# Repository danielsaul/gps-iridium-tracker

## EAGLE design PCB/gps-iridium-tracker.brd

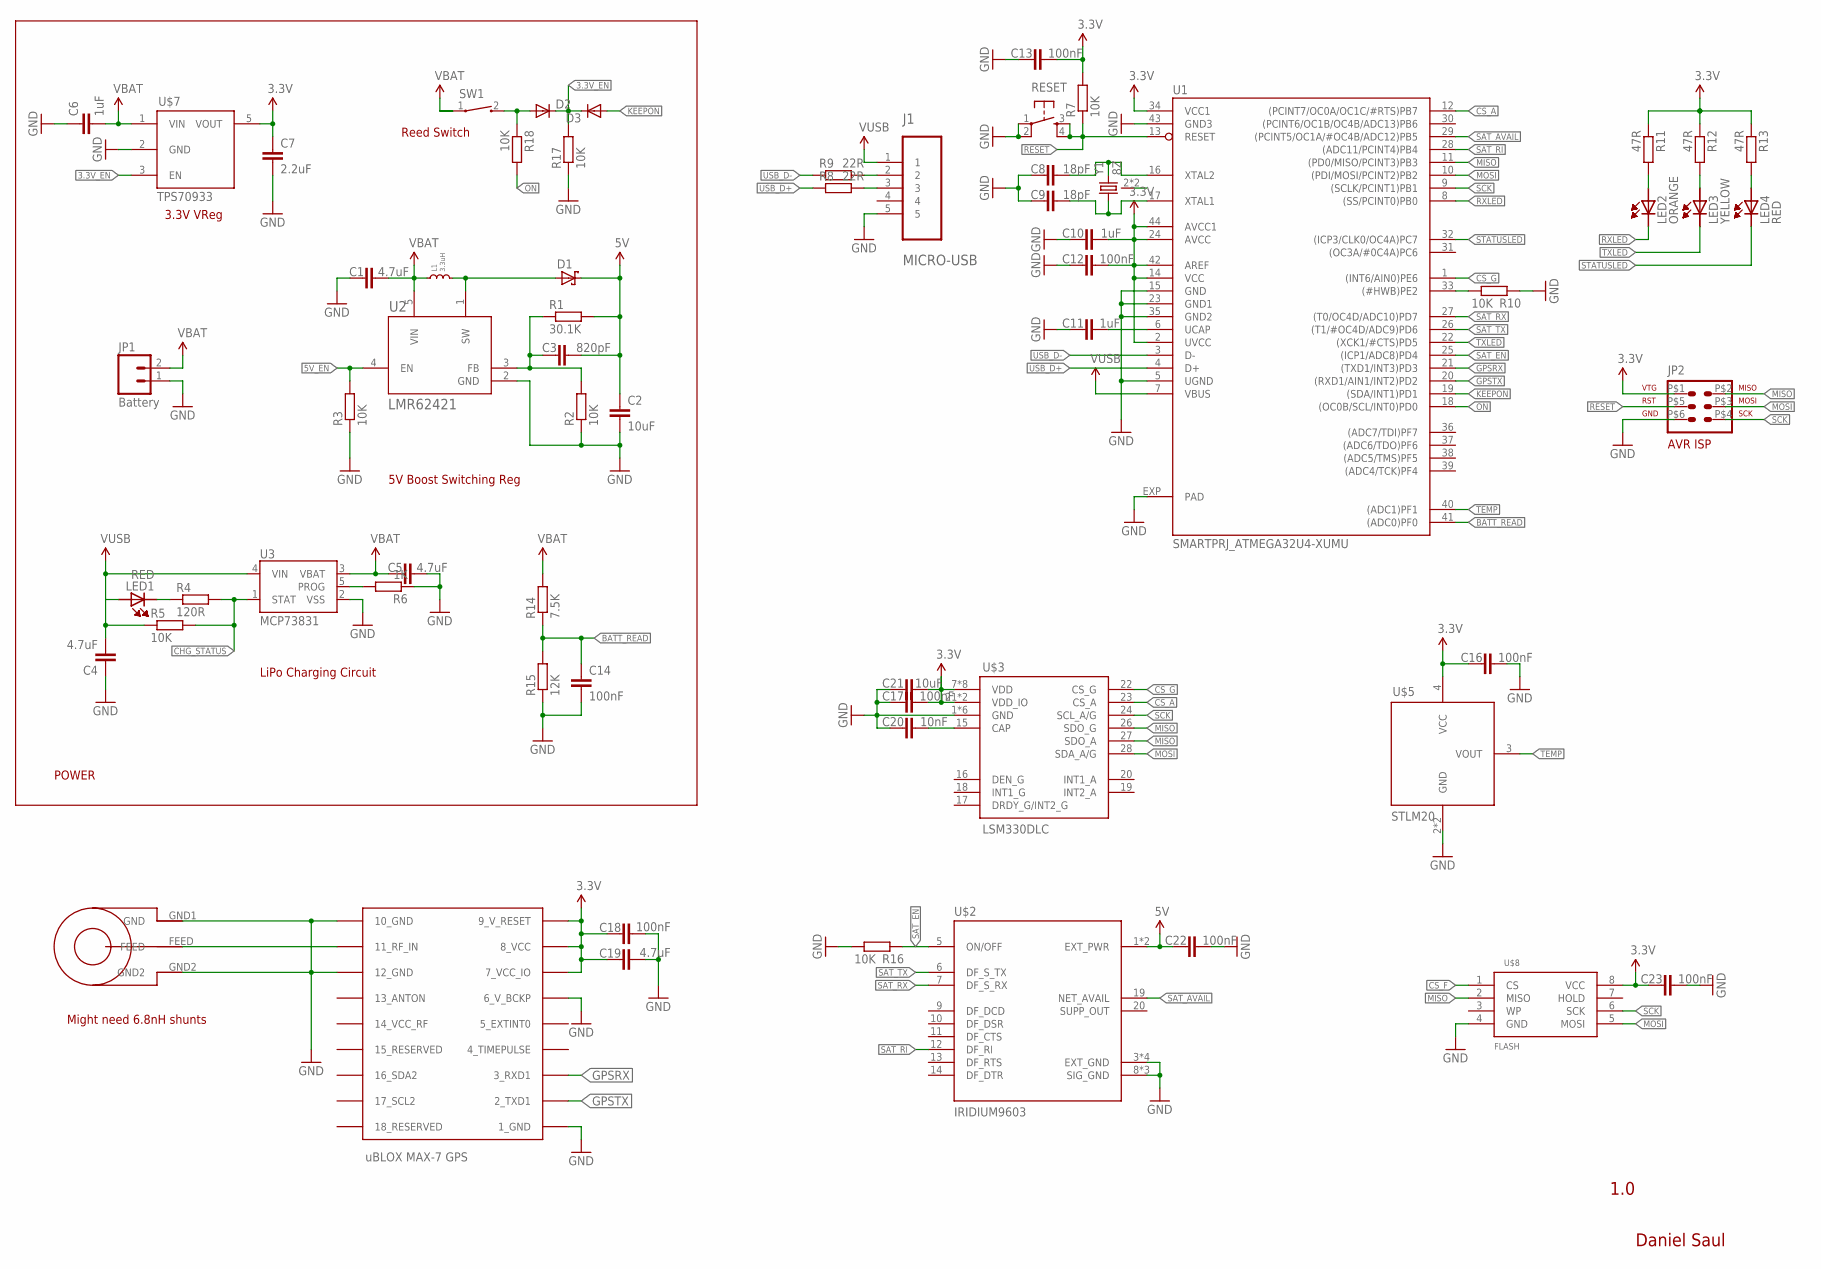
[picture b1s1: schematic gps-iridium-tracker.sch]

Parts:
C1, C4, C5: 4.7uF; 0603-CAP
C2: 10uF; 0603-CAP
C3: 820pF; 0603-CAP
C6: 1uF; 0603-CAP
C7: 2.2uF; 0603-CAP
C8, C9: 18pF; 0603-CAP
C10, C11: 1uF; 0402-CAP
C12, C13, C14, C16, C17, C18, C22, C23: 100nF; 0402-CAP
C19: 4.7uF; 0805
C20: 10nF; 0402-CAP
C21: 10uF; 0402-CAP
D1: B220A-13-F; SMA-DIODE
D2, D3: DIODESOD; SOD-323
GPS: UBLOX_MAX-6
J1: MICRO-USB; MOLEX_47346-0001
JP1: Battery; JST-2-PTH
JP2: AVR-ISP-6SMD; ICSPSMD
L1: 3.3uH; SRN3015
LED1, LED4: RED; R0402
LED2: ORANGE; R0402
LED3: YELLOW; R0402
R1: 30.1K; R0402
R2, R3, R5, R7, R10, R16, R17, R18: 10K; R0402
R4: 120R; R0402
R6: 1K; R0402
R8, R9: 22R; R0402
R11, R12, R13: 47R; R0402
R14: 7.5K; R0402
R15: 12K; R0402
RESET: KMR441NGLFS
SW1: CT10-XXXX-G1
U1: SMARTPRJ_ATMEGA32U4-XUMU; SMARTPRJ_QFN44ML7X7
U2: LMR62421; MF05A
U3: MCP73831; SOT23-5
U$1: JTI_ANTENNA-1575AT54A0010
U$2: IRIDIUM9603
U$3: LSM330DLC; LGA-28L
U$5: STLM20; SOT23-5L
U$7: TPS70933; SOT23-5L
U$8: FLASH; SO08
Y1: 8Z

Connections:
3.3V: C7.1, C10.2, C12.2, C13.2, C16.1, C17.2, C18.1, C19.1, C21.2, C23.1, GPS.7_VCC_IO, GPS.8_VCC, GPS.9_V_RESET, JP2.P$1 (2), R7.2, R11.1, R12.1, R13.1, U1.2 (UVCC), U1.14 (VCC), U1.24 (AVCC), U1.34 (VCC1), U1.42 (AREF), U1.44 (AVCC1), U$3.7 (VDD), U$3.8 (VDD), U$3.9 (VDD), U$3.10 (VDD), U$3.11 (VDD), U$3.12 (VDD), U$3.13 (VDD), U$3.14 (VDD), U$3.21 (VDD_IO), U$3.25 (VDD_IO), U$5.4 (VCC), U$7.5 (VOUT), U$8.8 (VCC)
3.3V_EN: D2.1 (C), D3.1 (C), R17.2, U$7.3 (EN)
5V: C2.1, C3.2, C22.1, D1.2 (C), R1.2, U$2.1 (EXT_PWR), U$2.2 (EXT_PWR)
5V_EN: R3.2, U2.4 (EN)
BATT_READ: C14.1, R14.1, R15.2, U1.41 ((ADC0)PF0)
CHG_STATUS: R4.2, R5.2, U3.1 (STAT)
CS_A: U1.12 ((PCINT7/OC0A/OC1C/#RTS)PB7), U$3.23 (CS_A)
CS_F: U$8.1 (CS)
CS_G: U1.1 ((INT6/AIN0)PE6), U$3.22 (CS_G)
GND: C1.1, C2.2, C4.1, C5.2, C6.1, C7.2, C8.1, C9.1, C10.1, C11.1, C12.1, C13.1, C14.2, C16.2, C17.1, C18.2, C19.2, C20.1, C21.1, C22.2, C23.2, GPS.1_GND, GPS.6_V_BCKP, GPS.10_GND, GPS.12_GND, J1.5, JP1.1, JP2.P$6 (6), R2.1, R3.1, R6.1, R10.1, R15.1, R16.2, R17.1, RESET.1, RESET.2 (P1), U1.5 (UGND), U1.15 (GND), U1.23 (GND1), U1.35 (GND2), U1.43 (GND3), U1.EXP (PAD), U2.2 (GND), U3.2 (VSS), U$1.GND1 (GND), U$1.GND2, U$2.3 (EXT_GND), U$2.4 (EXT_GND), U$2.8 (SIG_GND), U$2.15 (SIG_GND), U$2.18 (SIG_GND), U$2.HOLE1 (EXT_GND), U$2.HOLE2 (EXT_GND), U$3.1 (GND), U$3.2 (GND), U$3.3 (GND), U$3.4 (GND), U$3.5 (GND), U$3.6 (GND), U$5.2 (GND), U$5.5 (GND), U$7.2 (GND), U$8.4 (GND), Y1.2 (GND), Y1.4 (GND)
GPSRX: GPS.3_RXD1, U1.21 ((TXD1/INT3)PD3)
GPSTX: GPS.2_TXD1, U1.20 ((RXD1/AIN1/INT2)PD2)
KEEPON: D3.2 (A), U1.19 ((SDA/INT1)PD1)
MISO: JP2.P$2 (1), U1.11 ((PD0/MISO/PCINT3)PB3), U$3.26 (SDO_G), U$3.27 (SDO_A), U$8.2 (MISO)
MOSI: JP2.P$3 (4), U1.10 ((PDI/MOSI/PCINT2)PB2), U$3.28 (SDA_A/G), U$8.5 (MOSI)
unnamed: GPS.11_RF_IN, U$1.FEED
unnamed: D1.1 (A), L1.2, U2.1 (SW)
unnamed: C3.1, R1.1, R2.2, U2.3 (FB)
unnamed: LED1.1 (C), R4.1
unnamed: R6.2, U3.5 (PROG)
unnamed: C8.2, U1.16 (XTAL2), Y1.3 (2)
unnamed: C9.2, U1.17 (XTAL1), Y1.1
unnamed: C11.2, U1.6 (UCAP)
unnamed: J1.2, R9.2
unnamed: J1.3, R8.2
unnamed: R10.2, U1.33 ((#HWB)PE2)
unnamed: C20.2, U$3.15 (CAP)
unnamed: LED4.2 (A), R13.2
unnamed: LED2.2 (A), R11.2
unnamed: LED3.2 (A), R12.2
unnamed: D2.2 (A), R18.1, SW1.2
ON: R18.2, U1.18 ((OC0B/SCL/INT0)PD0)
RESET: JP2.P$5 (5), R7.1, RESET.3 (S), RESET.4 (S1), U1.13 (RESET)
RXLED: LED2.1 (C), U1.8 ((SS/PCINT0)PB0)
SAT_AVAIL: U1.29 ((PCINT5/OC1A/#OC4B/ADC12)PB5), U$2.19 (NET_AVAIL)
SAT_EN: R16.1, U1.25 ((ICP1/ADC8)PD4), U$2.5 (ON/OFF)
SAT_RI: U1.28 ((ADC11/PCINT4)PB4), U$2.12 (DF_RI)
SAT_RX: U1.27 ((T0/OC4D/ADC10)PD7), U$2.7 (DF_S_RX)
SAT_TX: U1.26 ((T1/#OC4D/ADC9)PD6), U$2.6 (DF_S_TX)
SCK: JP2.P$4 (3), U1.9 ((SCLK/PCINT1)PB1), U$3.24 (SCL_A/G), U$8.6 (SCK)
STATUSLED: LED4.1 (C), U1.32 ((ICP3/CLK0/OC4A)PC7)
TEMP: U1.40 ((ADC1)PF1), U$5.3 (VOUT)
TXLED: LED3.1 (C), U1.22 ((XCK1/#CTS)PD5)
USB_D+: R8.1, U1.4 (D+)
USB_D-: R9.1, U1.3 (D-)
VBAT: C1.2, C5.1, C6.2, JP1.2, L1.1, R14.2, SW1.1, U2.5 (VIN), U3.3 (VBAT), U$7.1 (VIN)
VUSB: C4.2, J1.1, LED1.2 (A), R5.1, U1.7 (VBUS), U3.4 (VIN)

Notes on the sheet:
uBLOX MAX-7 GPS
Daniel Saul
1.0
Might need 6.8nH shunts
LiPo Charging Circuit
5V Boost Switching Reg
POWER
3.3V VReg
Reed Switch

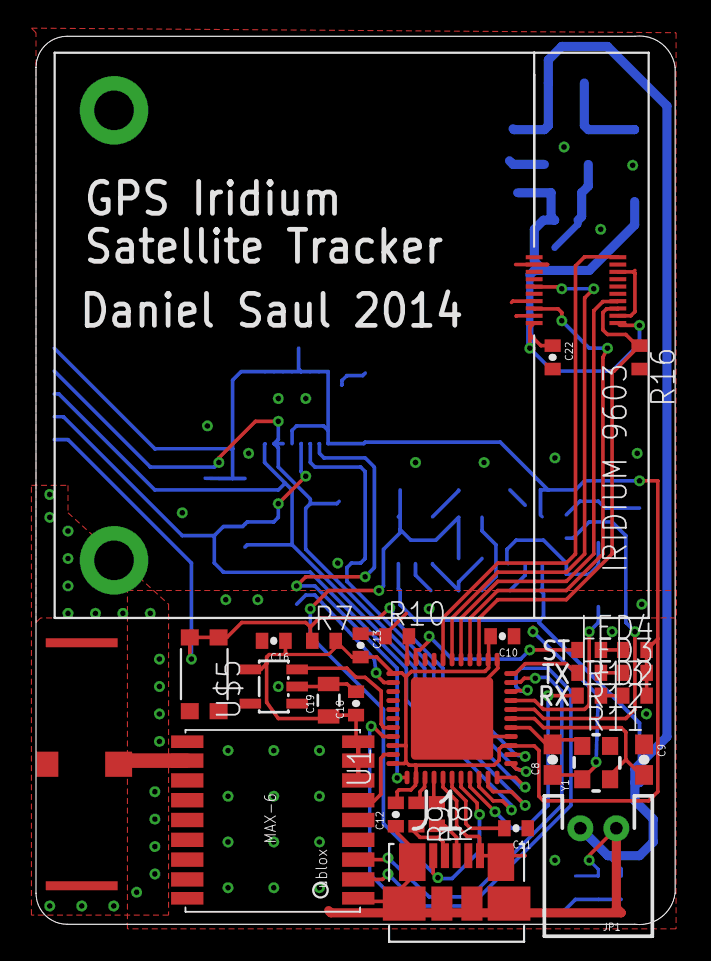
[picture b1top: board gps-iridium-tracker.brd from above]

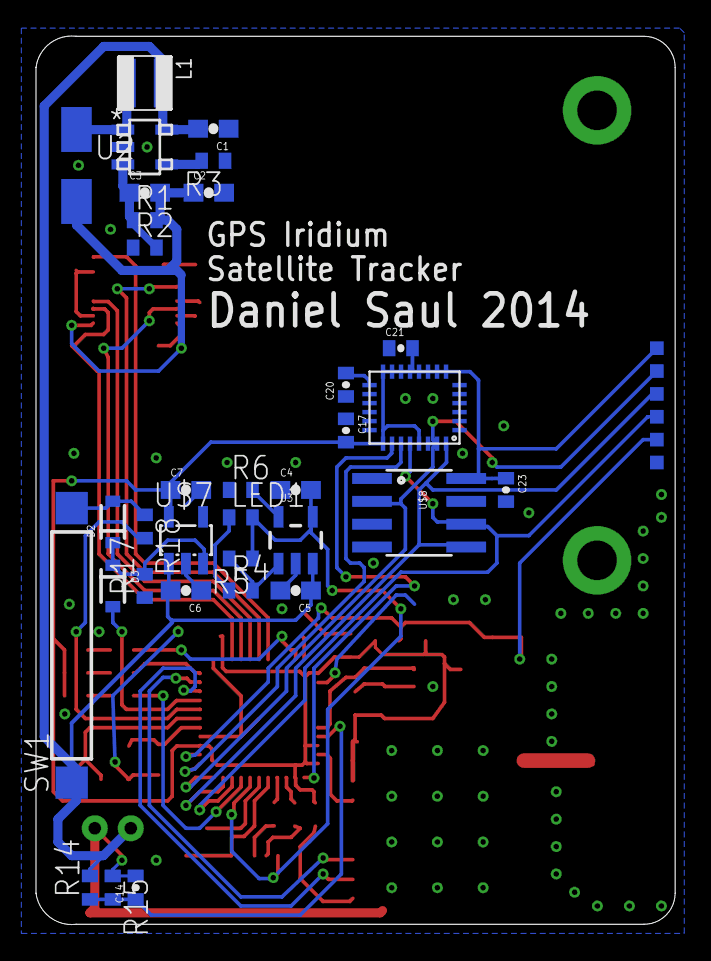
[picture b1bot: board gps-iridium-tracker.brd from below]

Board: 2 copper layers, 35.5 x 49.4 mm, 64 parts (34 on the bottom side), 46 nets.

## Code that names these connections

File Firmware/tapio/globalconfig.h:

/**
 * globalconfig.h
 *
 * Part of TapioTrack Prototype
 *
 * (C) Daniel Saul 2014
 * daniel@dansaul.co.uk
 *
 */

#ifndef GLOBALCONFIG_H
#define GLOBALCONFIG_H

// Debug settings
#define DEBUG_SERIAL        true
#define DEBUG_BAUD          115200
#define DEBUG_LED           true

// Pin Assignments - Arduino Leonardo Pins
// Power
#define PWR_ONSWITCH        3   //32u4 PD0
#define PWR_KEEPON          2   //32u4 PD1

//Analog
#define ANLG_BATT           A5  //32u4 PF0
#define ANLG_TEMP           A4  //32u4 PF1

// LEDs
#define LEDON               LOW
#define LEDOFF              HIGH
#define LED_STATUS          13  //32u4 PC7

// Chip Selects
#define CS_ACCEL            11  //32u4 PB7
#define CS_GYRO             7   //32u4 PE6

// Iridium
#define IRID_AVAIL          9   //32u4 PB5
#define IRID_RI             8   //32u4 PB4
#define IRID_EN             4   //32u4 PD4
#define IRID_RX             6   //32u4 PD7
#define IRID_TX             12  //32u4 PD6

#endif

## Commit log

2014-02-09 Started Schematic
2014-02-09 Deleted temp files
2014-02-19 Power done
2014-02-20 Bit more
2014-02-23 Started PCB
2014-03-01 Finished PCB
2014-03-06 Changed led resistor values
2014-03-06 v1 gerbers
2014-04-30 Started firmware

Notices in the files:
parts and their libraries:
SparkFun-Connectors: Licensing: CC v3.0 Share-Alike You are welcome to use this library for commercial purposes.
